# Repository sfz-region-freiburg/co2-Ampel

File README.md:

# CO2 Ampel
Hier findest du alle Informationen zur CO2 Ampel des Schülerforschungszentrum Region Freiburg e.V.

## Struktur
* [documentation](https://github.com/sfz-region-freiburg/co2-Ampel/tree/main/documentation) (Anleitungen und andere Dokumente)
* [electronic](https://github.com/sfz-region-freiburg/co2-Ampel/tree/main/electronics) (Schaltplan, PCB-Layout, EAGLE Daten, Gerber Daten)
* [firmware](https://github.com/sfz-region-freiburg/co2-Ampel/tree/main/firmware/CO2_Ampel_Display_1.5) (Arduino Code)
* [images](https://github.com/sfz-region-freiburg/co2-Ampel/tree/main/images) (Bilder und Grafiken)

## Die CO2 Ampel

## Funktion der CO2 Ampel
* Ampelfarbe entsprechend der Raumluftqualität
* Bei überschreiten von 1000 ppm akustisches Signal (alle 5 Minuten) Blitzlicht (alle 5 Sekunden)
* Akkulaufzeit von ca. 20 Stunden

Hintergrundinformationen:
Außenluft hat üblicherweise eine CO2 Konzentration von 350 bis 450 ppm.

**Richtwerte für Raumluftqualität:**

kleiner 800 ppm | gut
800-1000 ppm | mittel
größer 1000 ppm | mäßig 
Spätestens jetzt sollte gelüftet werden.

## Details zum Aufbau 
[Findest du unter documentation](https://github.com/sfz-region-freiburg/co2-Ampel/tree/main/documentation)

# Gefördert durch:

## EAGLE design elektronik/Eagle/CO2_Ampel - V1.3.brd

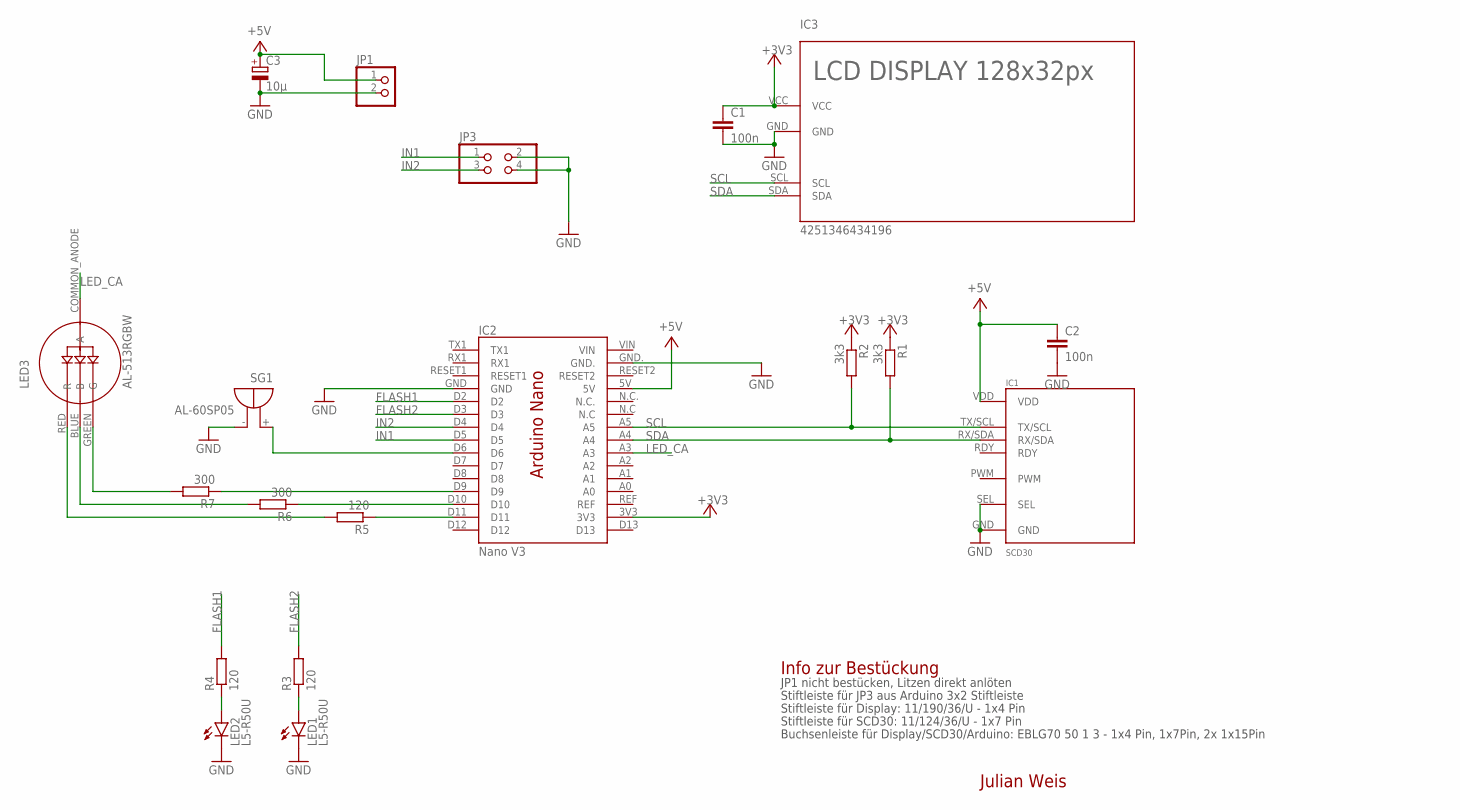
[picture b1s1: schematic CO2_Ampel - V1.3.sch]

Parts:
C1, C2: 100n; C050-025X075
C3: 10µ; E2-5
IC1: SCD30
IC2: Nano V3; ARDUINO_NANO
IC3: 4251346434196; 0.91INCH_128X32_I2C_12X38MM
JP1: PINHD-1X2; 1X02
JP3: PINHD-2X2; 2X02
LED1: L5-R50U; LED5MM_LIEGEND
LED2: L5-R50U; LED5MM_LIEGEND_GESPIEGELT
LED3: AL-513RGBW; LED-4_PIN
R1, R2: 3k3; 0207/10
R3, R4, R5: 120; 0207/10
R6, R7: 300; 0207/10
SG1: AL-60SP05; F/TMB

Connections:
+3V3: C1.1, IC2.3V3, IC3.VCC, R1.1, R2.1
+5V: C2.1, C3.+, IC1.VDD, IC2.5V, JP1.1
FLASH1: IC2.D2, R4.2
FLASH2: IC2.D3, R3.2
GND: C1.2, C2.2, C3.-, IC1.GND, IC1.SEL, IC2.GND., IC3.GND, JP1.2, JP3.2, JP3.4, LED1.K (C), LED2.K (C), SG1.-
IN1: IC2.D5, JP3.1
IN2: IC2.D4, JP3.3
LED_CA: IC2.A3, LED3.COMMON_ANODE (A)
unnamed: LED3.RED (R), R5.2
unnamed: LED3.BLUE (B), R6.2
unnamed: LED2.A, R4.1
unnamed: LED1.A, R3.1
unnamed: LED3.GREEN (G), R7.2
unnamed: IC2.D9, R7.1
unnamed: IC2.D10, R6.1
unnamed: IC2.D11, R5.1
unnamed: IC2.D6, SG1.+
SCL: IC1.TX/SCL, IC2.A5, IC3.SCL, R2.2
SDA: IC1.RX/SDA, IC2.A4, IC3.SDA, R1.2

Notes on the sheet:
Stiftleiste für Display: 11/190/36/U - 1x4 Pin
Stiftleiste für SCD30: 11/124/36/U - 1x7 Pin
Buchsenleiste für Display/SCD30/Arduino: EBLG70 50 1 3 - 1x4 Pin, 1x7Pin, 2x 1x15Pin
Info zur Bestückung
Stiftleiste für JP3 aus Arduino 3x2 Stiftleiste
JP1 nicht bestücken, Litzen direkt anlöten

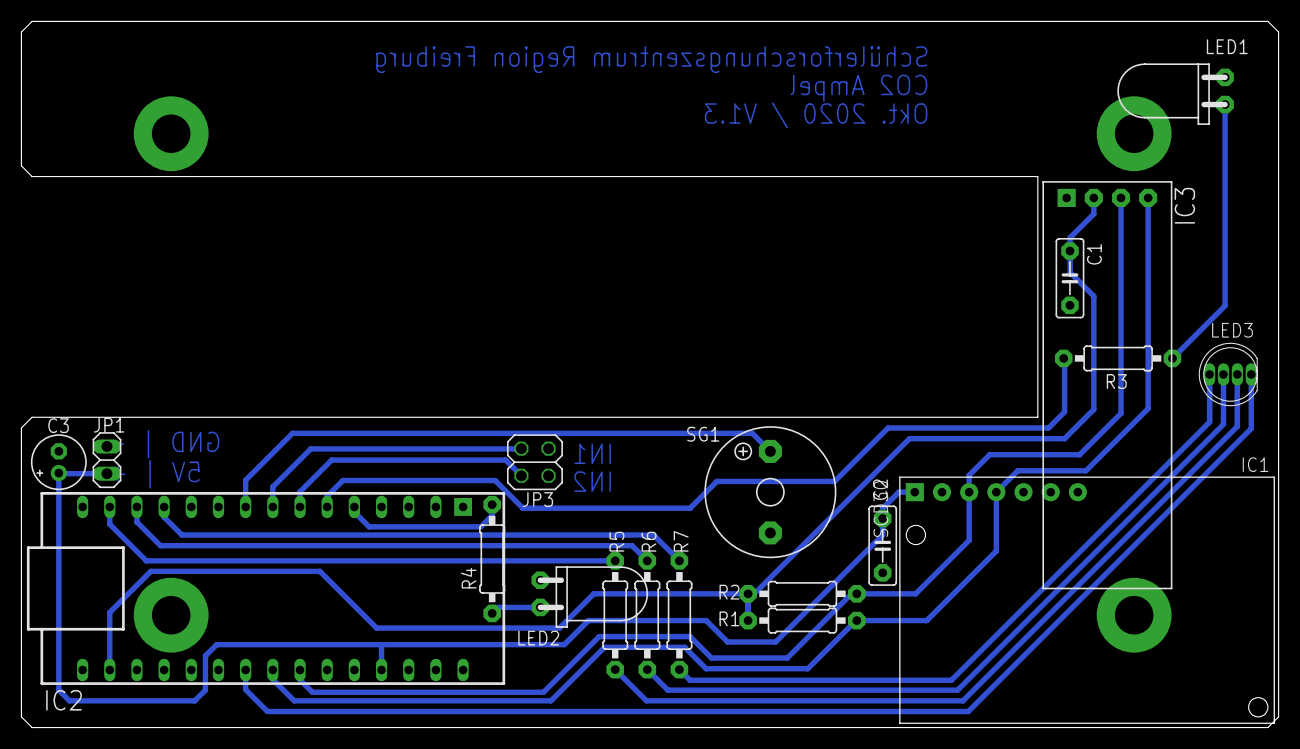
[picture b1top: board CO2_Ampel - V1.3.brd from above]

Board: 2 copper layers, 117.5 x 66.0 mm, 19 parts (0 on the bottom side), 19 nets.

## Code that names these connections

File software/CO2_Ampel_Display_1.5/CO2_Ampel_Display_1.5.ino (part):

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#define LED_R 11  // RGB-LED RED, Pin D11
#define LED_G 9  // RGB-LED GREEN, Pin D9
#define LED_B 10  // RGB-LED BLUE, Pin D10
#define LED_CA A3 // RGB-LED Common Anode, Pin A3
#define BUZZER 6  // Buzzer pin D6
#define FLASH1 2 // Red Flash LED, pin D2, near Display
#define FLASH2 3 // Red Flash LED, pin D3, near Arduino
#define IN1 5 // Jumper input IN1, not used at the moment
#define IN2 4 // Jumper input IN2, not used at the moment

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  pinMode(LED_R, OUTPUT);
  pinMode(LED_G, OUTPUT);
  pinMode(LED_B, OUTPUT);
  pinMode(LED_CA, OUTPUT);
  pinMode(FLASH1, OUTPUT);
  pinMode(FLASH2, OUTPUT);
  pinMode(IN1, INPUT_PULLUP);   //not used at the moment
  pinMode(IN2, INPUT_PULLUP);   //not used at the moment
  pinMode(BUZZER, OUTPUT);
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
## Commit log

2021-03-11 Initial upload
2021-03-11 README update
2021-03-11 README.md update
2021-03-11 README.md update der Formatierung
2021-03-11 README.md Formatierung angepasst
2021-03-11 Neue Ordnerstruktur
2021-03-11 Update Doku
2021-03-11 update Documentation
2021-03-11 Docu update
